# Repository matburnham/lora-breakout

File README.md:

# DRF1278F and XL1278-SMT LoRa breakout board

A somewhat 'universal' breakout board to adapt Dorji DRF1278F and XL1278-SMT modules to standard 0.1" matrix breadboard or stripboard format.

# Module identification

Note: while the DRF1278F and XL1278-SMT boards look similar, the pinouts are significantly different.

## Confusion

There is a lot of confusion between Ebay and AliExpress sellers alike. One ebay seller even showing photos of both types of boards on the same listing. So check carefully, or use what you're given with this either/or breakout.

## Documentation

CI/CD documentation generation 

TODO: links to generated documentation, etc.

# Libraries

* KiCad symbol and footprint libraries for DRF1278F and XL1278-SMT for KiCad are at [kicad-libs](https://github.com/matburnham/kicad-libs)

# References

* Inspired by Stuart Robinson's Breadboard Friendly DRF1278 Board [Tindie](https://www.tindie.com/products/stuartsprojects/breadboard-friendly-board-for-dorji-drf1278-module/) | [GitHub](https://github.com/StuartsProjects/Devices/tree/master/Breadboard%20Friendly%20DRF1278%20Board)

* [Dorji DRF1278F datasheet](http://www.dorji.com/docs/data/DRF1278F.pdf) | [respository copy](Docs/DRF1278F.pdf)
* Closest information to a [XL1278-SMT datasheet](http://www.hr-wt.com/html_products/XL1278-SMT-59.html) | [respository screenshot](Docs/screencapture-hr-wt-html-products-XL1278-SMT-59-html-2021-02-26-15_49_33.png)

* [A Review of the Mini SX1278 LoRa Transceiver Module](https://www.electroschematics.com/rf-radio-frequency/)

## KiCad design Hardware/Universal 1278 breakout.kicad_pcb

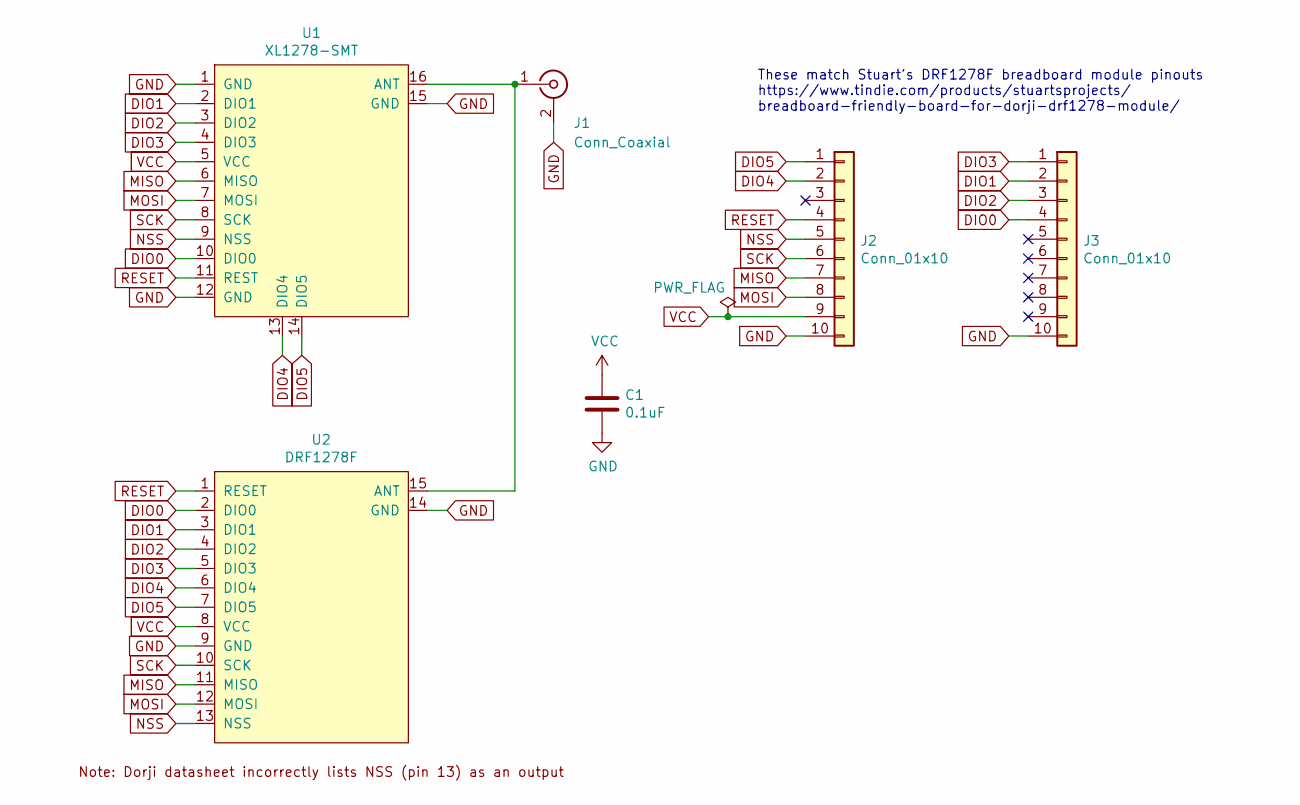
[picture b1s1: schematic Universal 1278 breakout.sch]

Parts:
C1: 0.1uF; C_0603_HandSoldering
J1: Conn_Coaxial; SMA_EdgeMount_Holes
J2, J3: Conn_01x10; PinHeader_1x10_P2.54mm_Vertical
U1: XL1278-SMT
U2: DRF1278F

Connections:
DIO0: J3.4, U1.10 (DIO0), U2.2 (DIO0)
DIO1: J3.2, U1.2 (DIO1), U2.3 (DIO1)
DIO2: J3.3, U1.3 (DIO2), U2.4 (DIO2)
DIO3: J3.1, U1.4 (DIO3), U2.5 (DIO3)
DIO4: J2.2, U1.13 (DIO4), U2.6 (DIO4)
DIO5: J2.1, U1.14 (DIO5), U2.7 (DIO5)
GND: C1.2, J1.2 (Ext), J2.10, J3.10, U1.1 (GND), U1.12 (GND), U1.15 (GND), U2.9 (GND), U2.14 (GND)
MISO: J2.7, U1.6 (MISO), U2.11 (MISO)
MOSI: J2.8, U1.7 (MOSI), U2.12 (MOSI)
NSS: J2.5, U1.9 (NSS), U2.13 (NSS)
unnamed: J1.1 (In), U1.16 (ANT), U2.15 (ANT)
RESET: J2.4, U1.11 (REST), U2.1 (RESET)
SCK: J2.6, U1.8 (SCK), U2.10 (SCK)
VCC: C1.1, J2.9, U1.5 (VCC), U2.8 (VCC)

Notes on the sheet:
These match Stuart's DRF1278F breadboard module pinouts https://www.tindie.com/products/stuartsprojects/ breadboard-friendly-board-for-dorji-drf1278-module/

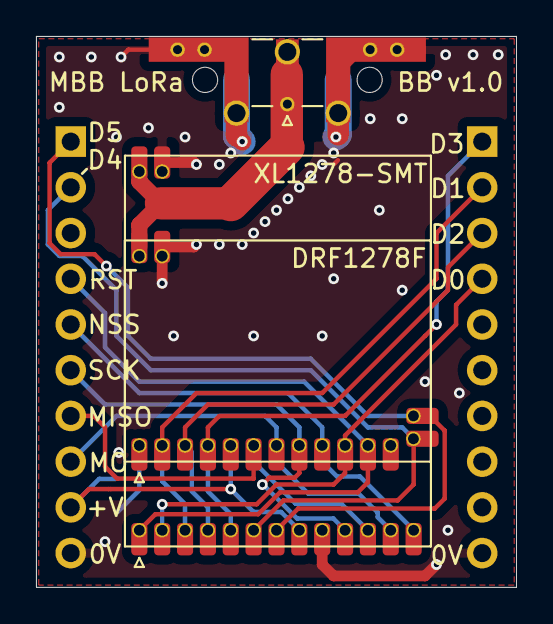
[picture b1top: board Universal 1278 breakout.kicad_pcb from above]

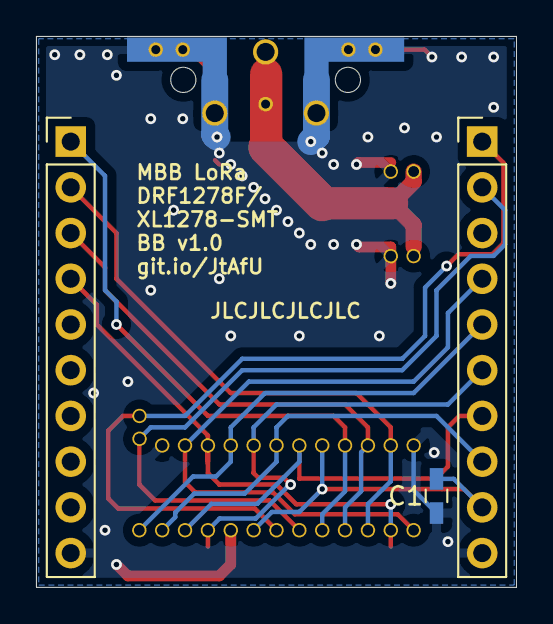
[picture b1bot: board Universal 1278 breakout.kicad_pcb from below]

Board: 2 copper layers, 26.7 x 30.6 mm, 6 parts (3 on the bottom side), 14 nets.

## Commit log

2021-02-26 Initial commit of board to get GitHub Actions, etc. up and running and shelve project before doing final pieces (ground pour, antenna holes, etc.)
2021-02-26 GitHub actions workflow
2021-02-26 Allow manual run
2021-02-26 Update README.md
    Add documentation generation status indicator
2021-02-26 Can't find PCB files - does it even need the optional parameters?
2021-02-26 Try ** to find PCB files
2021-02-26 Try assuming it's the root
2021-02-26 Fix (most) DRC errors.
2021-02-26 Ground pour. All DRC errors fixed except courtyards. Ignore courtyard warnings.
2021-02-26 Revert global filter that can't be there in the .yml Try turning off courtyard prohibition in project and see if CI picks this up instead.
2021-02-26 Fix all DRC violations - missing connections
2021-02-26 Add Cmts.User layer
2021-02-26 Fix badge updating
2021-02-26 Revert output directory
2021-02-26 Images for README
2021-02-26 Rename.
2021-02-26 Smaller images
2021-02-26 Rotate
2021-02-26 Documentation
2021-02-26 Description
2021-02-27 Various updates.
2021-02-27 Update.
2021-02-27 Further updates
2021-03-01 Rendered images
2021-03-01 Fix antenna ground connections
2021-03-01 Update renders
2021-03-01 Crop renders
2021-03-01 Add render images to README.md
2021-03-01 Fix more grounds.
